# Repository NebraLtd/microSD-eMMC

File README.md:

# microSD-eMMC
Open source Micro SD card to eMMC Adapter

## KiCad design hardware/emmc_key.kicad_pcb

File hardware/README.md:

# Micro SD card to eMMC Adapter Hardware KiCad Design

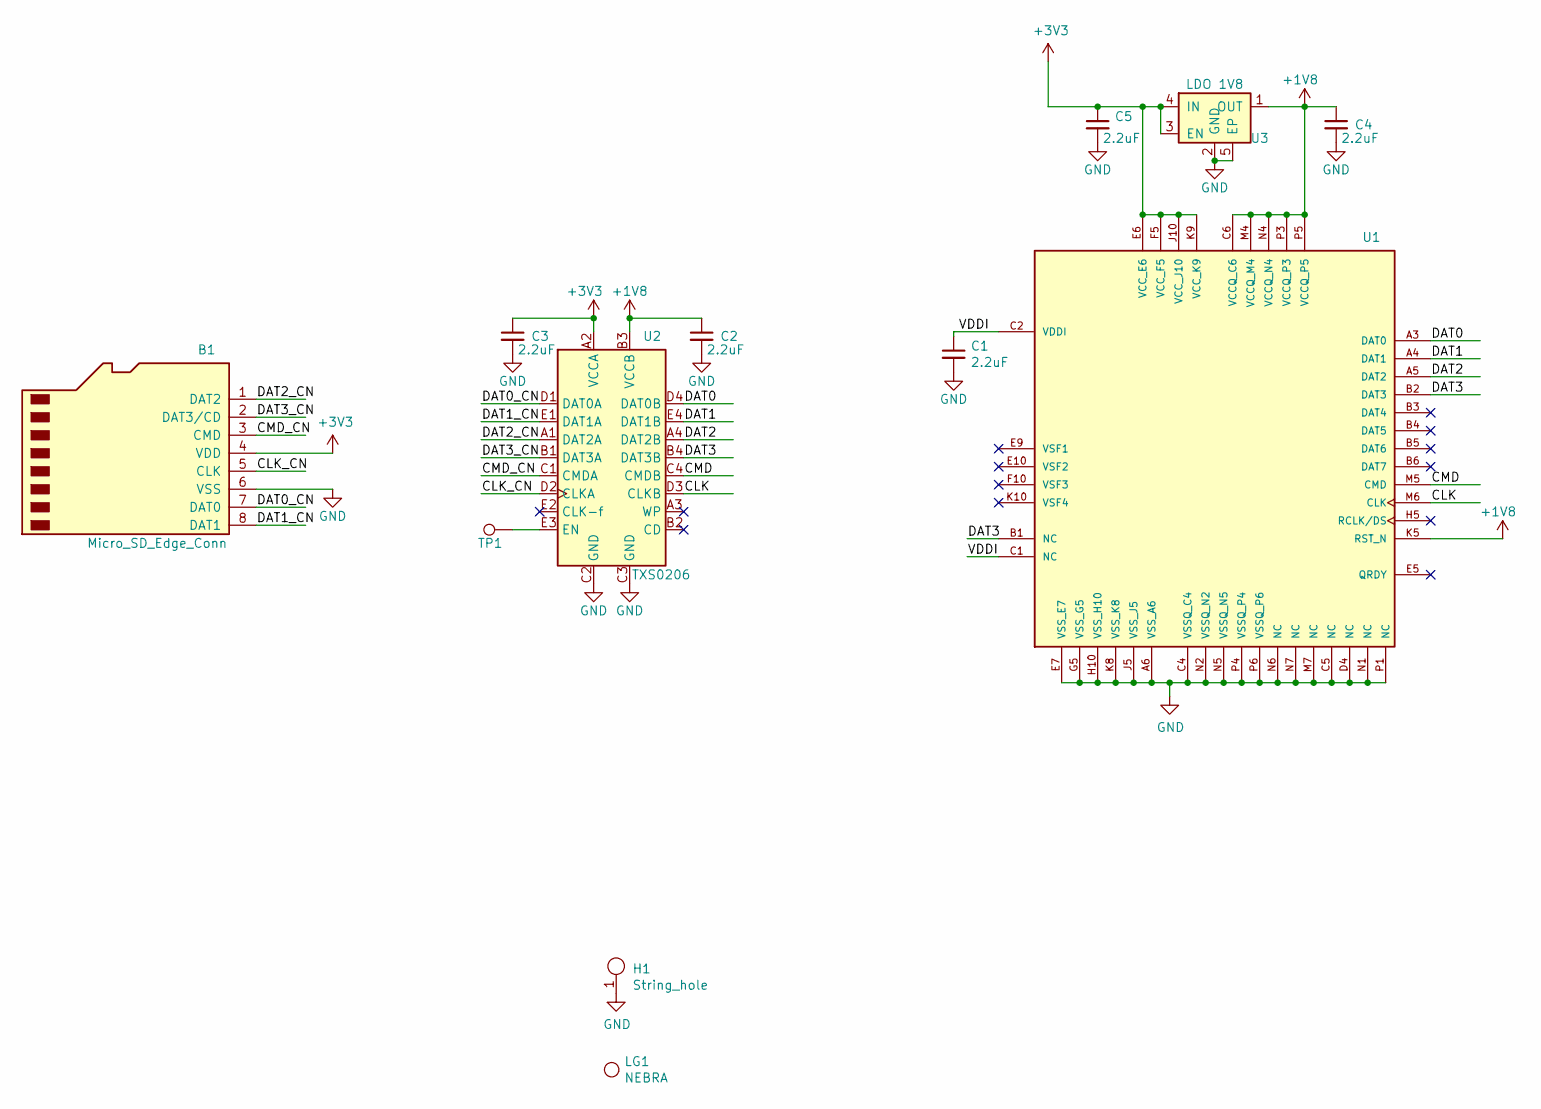
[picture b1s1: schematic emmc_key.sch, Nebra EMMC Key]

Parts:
B1: Micro_SD_Edge_Conn; MICRO_SD_EDGE
C1, C2, C3, C4, C5: 2.2uF; C_0402_1005Metric; Part Number CL05A225MP5NSNC
H1: String_hole; MountingHole_2.2mm_M2
LG1: NEBRA; NEBRA_LOGO
TP1: TestPoint; TestPoint_Pad_D1.0mm
U1: EMMC Module; BGA153N50P14X14_1150X1300X80; Part Number THGAMRG8T13BAIL
U2: TXS0206; BGA20N40P5X4_195X155X50N; Part Number TXS0206YFPR
U3: LDO 1V8; UDFN-4-1EP_1x1mm_P0.65mm_EP0.48x0.48mm; Part Number NCP177AMX180TCG

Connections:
+1V8: C2.1, C4.1, U1.C6 (VCCQ_C6), U1.K5 (RST_N), U1.M4 (VCCQ_M4), U1.N4 (VCCQ_N4), U1.P3 (VCCQ_P3), U1.P5 (VCCQ_P5), U2.B3 (VCCB), U3.1 (OUT)
+3V3: B1.4 (VDD), C3.1, C5.1, U1.E6 (VCC_E6), U1.F5 (VCC_F5), U1.J10 (VCC_J10), U1.K9 (VCC_K9), U2.A2 (VCCA), U3.3 (EN), U3.4 (IN)
/CLK: U1.M6 (CLK), U2.D3 (CLKB)
/CLK_CN: B1.5 (CLK), U2.D2 (CLKA)
/CMD: U1.M5 (CMD), U2.C4 (CMDB)
/CMD_CN: B1.3 (CMD), U2.C1 (CMDA)
/DAT0: U1.A3 (DAT0), U2.D4 (DAT0B)
/DAT0_CN: B1.7 (DAT0), U2.D1 (DAT0A)
/DAT1: U1.A4 (DAT1), U2.E4 (DAT1B)
/DAT1_CN: B1.8 (DAT1), U2.E1 (DAT1A)
/DAT2: U1.A5 (DAT2), U2.A4 (DAT2B)
/DAT2_CN: B1.1 (DAT2), U2.A1 (DAT2A)
/DAT3: U1.B1 (NC), U1.B2 (DAT3), U2.B4 (DAT3B)
/DAT3_CN: B1.2 (DAT3/CD), U2.B1 (DAT3A)
/VDDI: C1.1, U1.C1 (NC), U1.C2 (VDDI)
GND: B1.6 (VSS), C1.2, C2.2, C3.2, C4.2, C5.2, H1.1, U1.A6 (VSS_A6), U1.C4 (VSSQ_C4), U1.C5 (NC), U1.D4 (NC), U1.E7 (VSS_E7), U1.G5 (VSS_G5), U1.H10 (VSS_H10), U1.J5 (VSS_J5), U1.K8 (VSS_K8), U1.M7 (NC), U1.N1 (NC), U1.N2 (VSSQ_N2), U1.N5 (VSSQ_N5), U1.N6 (NC), U1.N7 (NC), U1.P1 (NC), U1.P4 (VSSQ_P4), U1.P6 (VSSQ_P6), U2.C2 (GND), U2.C3 (GND), U3.2 (GND), U3.5 (EP)
unnamed: TP1.1, U2.E3 (EN)

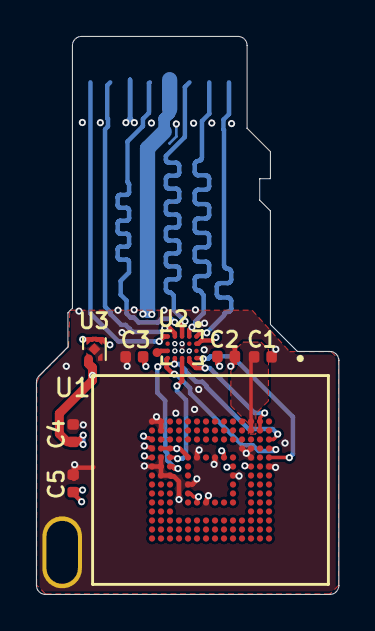
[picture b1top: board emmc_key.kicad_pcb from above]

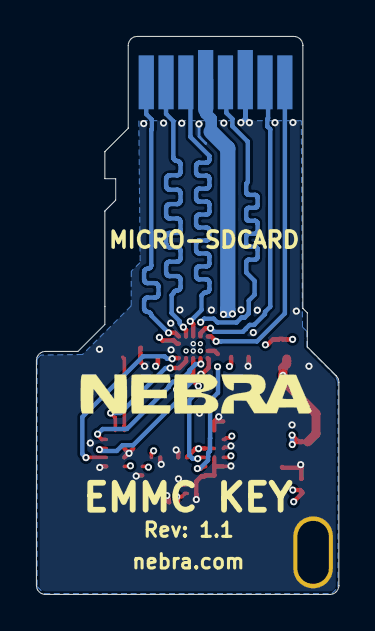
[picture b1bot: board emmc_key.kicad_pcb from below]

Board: 4 copper layers, 16.8 x 31.0 mm, 12 parts (2 on the bottom side), 17 nets.

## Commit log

2021-04-16 Initial Design Rev:1.0
2021-04-16 Schematic pdf
2021-05-12 Gerber bottom mask added, PCB thickness specified to 0.8mm.
2021-06-09 RST_N connected to 3V3. Fabrication outputs regenerated.
2021-07-05 New variant with voltage translator and 1V8 LDO for eMMC modules where VCCQ is 1V8.
2021-07-20 Changed 0.15 vias from blind to TH.
